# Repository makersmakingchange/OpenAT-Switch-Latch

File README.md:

<!--- Open Source Assistive Technology: GitHub Readme Template Version 1.2 (2024-May-27)  --->

<!--- TITLE --->
# OpenAT Switch Latch 
The OpenAT Switch Latch is a switch adapter that enables a standard momentary assistive switch to be used as a toggle switch or latch. Activating and releasing the input switch will turn on and hold on the output. Activating and releasing the input switch again will turn the connected output device off. The device requires one CR2032 coin cell battery for operation. 

This device was developed as several assistive switch users requested the ability to control lights and other devices in a semi-permanent manner utilizing their preferred momentary assistive switches.

The OpenAT Switch Latch is comprised of off-the-shelf electronics, a custom printed circuit board (PCB) and 3D printed parts.

The OpenAT Switch Latch is open assistive technology (OpenAT). Under the terms of the open source licenses, the device may be built, used, and improved upon by anyone.

The overall cost of materials for a single build is approximately $67 CAD. The cost of materials when built in quantity is $38 CAD.

> [!IMPORTANT]
2025-Nov-06: One of the electronic components in this design has been discontinued (MOSFET IRLD014PBF) and is no longer available on DigiKey or Mouser. In the short term, there are some alternative sources (e.g., https://www.amazon.ca/10PCS-IRLD110-DIP4-IRLD110PBF-DIP-4/dp/B0DSSJTPH8). In the longer term, we are working on updating the design with an alternative component.  

Last updated: 2026-Jan-12

## Usage
To setup the OpenAT Switch Latch, a momentary switch is plugged into the 3.5 mm jack marked 'Input' and the device to be controlled is plugged into the 3.5 mm jack marked 'Output'.

To use the device it must be powered on by sliding the Power Switch towards the left to the On position. When the assistive switch is activated, the LED indicator light will turn on and remain on, and the output device will be activated. When the assistive switch is activated again, the LED indicitor light will turn off and remain off, and the output device will be deactivated.

## More info at
- [Makers Making Change Library Page](https://www.makersmakingchange.com/s/product/switch-latch/01tJR00000095zlYAA)

## How to Obtain a OpenAT-Switch-Latch
### 1. Do it Yourself (DIY) or Do it Together (DIT)

This is an open-source assistive technology, so anyone is free to build it. All of the files and instructions required to build the OpenAT-Switch-Latch are contained within this repository. Refer to the Maker Checklist below.

### 2. Request a build of this device

If you would like to obtain a OpenAT Switch Latch, you may submit a build request through the [MMC Library Page](https://www.makersmakingchange.com/s/product/switch-latch/01tJR00000095zlYAA). The requestor is responsible for the cost of materials and any shipping.

### 3. How to build this device for someone else

If you have the skills and equipment to build this device, and would like to donate your time to create the switch for someone who needs it, visit the [MMC Maker Wanted](https://makersmakingchange.com/maker-wanted/) section.

## Getting Started

### 1. Read the Makers Checklist

The [Makers Checklist](/Documentation/OpenAT_Switch_Latch_Maker_Checklist.pdf) provides an overview of the steps required to build this device.

### 2. Order the Off-The-Shelf Components

The [Bill of Materials](/Documentation/OpenAT_Switch_Latch_BOM.csv) lists all of the parts and components required to build the OpenAT-Switch-Latch. The main switch component needs to be ordered online. The rest of the off-the-shelf components are also online or may be available in smaller quantities at your local hardware store or dollar store.

### 3. Order the PCBs

The [Gerber_Files](/Build_Files/PCB_Build_Files/Gerber_Files) includes the PCB build information which can be submitted to PCB fabrication service to create the custom PCB. Please refer to MMC-PCB for more information on custom PCB fabrication.

### 4. Print the 3D Printable components

All of the files and individual print files can be in the [/Build_Files/3D_Printing_Files](/Build_Files/3D_Printing_Files/) folder.

### 5. Assemble the OpenAT-Switch-Latch

Reference the [Assembly Guide](/Documentation/OpenAT_Switch_Latch_Assembly_Guide.pdf) for the tools and steps required to build each portion.

## Files

### Documentation
| Document             | Version | Link |
|----------------------|---------|------|
| Design Rationale     | 1.0     | [OpenAT_Switch_Latch_Design_Rationale](/Documentation/OpenAT_Switch_Latch_Design_Rationale.pdf)     |
| Maker Checklist      | 1.0     | [OpenAT_Switch_Latch_Maker_Checklist](/Documentation/OpenAT_Switch_Latch_Maker_Checklist.pdf)     |
| Bill of Materials    | 1.2.1    | [OpenAT_Switch_Latch_Bill_of_Materials](/Documentation/OpenAT_Switch_Latch_BOM.csv)     |
| 3D Printing Guide    | 1.0     | [OpenAT_Switch_Latch_3D_Printing_Guide](/Documentation/OpenAT_Switch_Latch_3D_Printing_Guide.pdf)     |
| Assembly Guide       | 1.2.1     | [OpenAT_Switch_Latch_Assembly_Guide](/Documentation/OpenAT_Switch_Latch_Assembly_Guide.pdf)     |
| User Guide           | 1.0     | [OpenAT_Switch_Latch_User_Guide](/Documentation/OpenAT_Switch_Latch_User_Guide.pdf)    |

### Design Files

 - [CAD Design Files](/Design_Files/CAD_Design_Files)
 - [PCB Design Files](/Design_Files/PCB_Design_Files)

### Build Files

 - [3D Printing Files](/Build_Files/3D_Printing_Files)
 - [PCB Build Files](/Build_Files/PCB_Build_Files)

## License
Copyright (c) 2023-2024 Neil Squire Society.

This repository describes Open Hardware:
 - Everything needed or used to design, make, test, or prepare the OpenAT Switch Latch is licensed under the [CERN 2.0 Weakly Reciprocal license (CERN-OHL-W v2) or later](https://cern.ch/cern-ohl ) .
  - Accompanying material such as instruction manuals, videos, and other copyrightable works that are useful but not necessary to design, make, test, or prepare the Forest Hub are published under a [Creative Commons Attribution-ShareAlike 4.0 license (CC BY-SA 4.0)](https://creativecommons.org/licenses/by-sa/4.0/) .

You may redistribute and modify this documentation and make products using it under the terms of the [CERN-OHL-W v2](https://cern.ch/cern-ohl).
This documentation is distributed WITHOUT ANY EXPRESS OR IMPLIED WARRANTY, INCLUDING OF MERCHANTABILITY, SATISFACTORY QUALITY AND FITNESS FOR A PARTICULAR PURPOSE.
Please see the CERN-OHL-W v2 for applicable conditions.

Source Location: https://github.com/makersmakingchange/OpenAT-Switch-Latch

## Contributors
 
 - Derrick Andrews, Neil Squire Society. Concept generation, circuit design, testing, documentation.
 - Milad Hajihassan, Neil Squire Society. PCB Layout.
 - Jake Mclvor, Neil Squire Society. Enclosure design, documentation. 

---

<!-- ABOUT MMC START -->
## About Makers Making Change

Makers Making Change is a program of [Neil Squire](https://www.neilsquire.ca/), a Canadian non-profit that uses technology, knowledge, and passion to empower people with disabilities.

Makers Making Change leverages the capacity of community based Makers, Disability Professionals and Volunteers to develop and deliver affordable Open Source Assistive Technologies.

 - Website: [www.MakersMakingChange.com](https://www.makersmakingchange.com/)
 - GitHub: [makersmakingchange](https://github.com/makersmakingchange)
 - Bluesky: [@makersmakingchange.bsky.social](https://bsky.app/profile/makersmakingchange.bsky.social)
 - Instagram: [@makersmakingchange](https://www.instagram.com/makersmakingchange)
 - Facebook: [makersmakechange](https://www.facebook.com/makersmakechange)
 - LinkedIn: [Neil Squire Society](https://www.linkedin.com/company/neil-squire-society/)
 - Thingiverse: [makersmakingchange](https://www.thingiverse.com/makersmakingchange/about)
 - Printables: [MakersMakingChange](https://www.printables.com/@MakersMakingChange)

### Contact Us
For technical questions, to get involved, or to share your experience we encourage you to [visit our website](https://www.makersmakingchange.com/) or [contact us](https://www.makersmakingchange.com/s/contact).
<!-- ABOUT MMC END -->

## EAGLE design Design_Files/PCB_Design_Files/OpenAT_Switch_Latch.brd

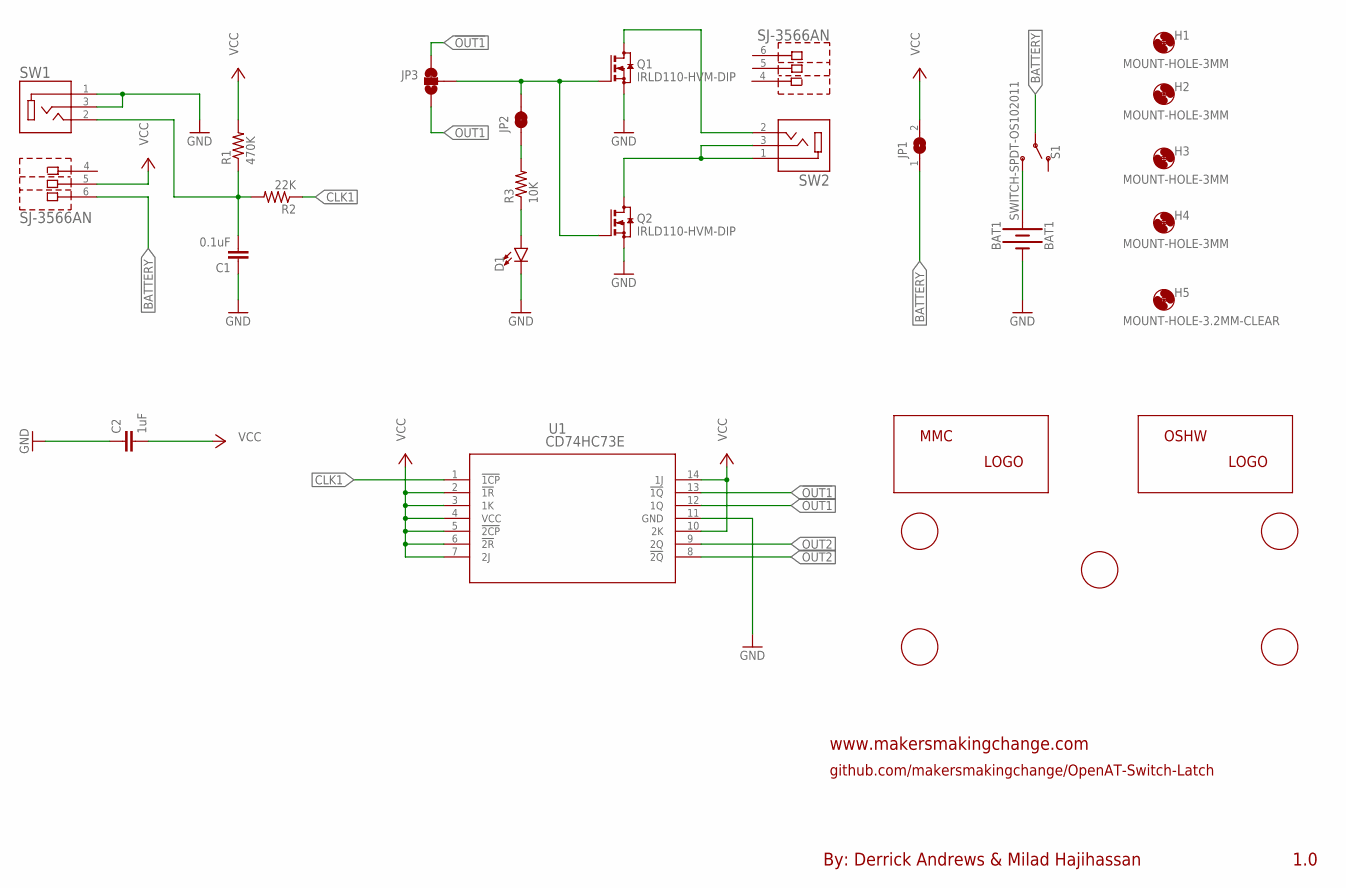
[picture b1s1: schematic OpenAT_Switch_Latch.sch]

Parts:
BAT1: BAT1; BATTCOM_20MM_PTH
C1: 0.1uF; CAP-050-030X075
C2: 1uF; CAP-050-030X075
D1: LED_5MM-5MM-GREEN; LED_5MM_GREEN
H1, H2, H3, H4: MOUNT-HOLE-3MM; HOLE-3MM
H5: MOUNT-HOLE-3.2MM-CLEAR; HOLE-3.2MM-CLEAR
JP1: SOLDERJUMPEROPENED; SOLDERJUMPER_OPENED_TRACE_SILK
JP2: JUMPERS-SMT_2_NC_TRACE_SILK; JUMPERS_SMT-JUMPER_2_NC_TRACE_SILK
JP3: JUMPERS-SMT_3_1-NC_TRACE_SILK; JUMPERS_SMT-JUMPER_3_1-NC_TRACE_SILK
LABEL_INPUT: MMC_LABEL-SW-INPUT; LABEL-INPUT
LABEL_LOGO: MMC_LOGO-SM; MMC_SMALL_LOGO
LABEL_OUTPUT: MMC_LABEL-SW-OUTPUT; LABEL-OUTPUT
Q1, Q2: IRLD110-HVM-DIP; HVM-DIP
R1: 470K; RESISTOR_0204/5
R2: 22K; RESISTOR_0204/5
R3: 10K; RESISTOR_0204/5
S1: SWITCH-SPDT-OS102011; SWITCH_SPDT_11MA1QS1
SW1, SW2: SJ-3566AN; CUI_SJ-3566AN
U1: CD74HC73E; 14-DIP
U$1: OSHW_LOGO-XSM; OSHW_X-SMALL_LOGO
U$2: MMC_LABEL-OPENAT; LABEL-OPENAT
U$3: MMC_LABEL-SWITCH-LATCH; LABEL-SWITCH-LATCH
U$4: MMC_LABEL-V1.0; LABEL-V1.0

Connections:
!OUT1: JP3.1, U1.13 (!1Q)
!OUT2: U1.8 (!2Q)
BATTERY: JP1.1, S1.2, SW1.6
CLK1: R2.1, U1.1 (!1CP)
GND: BAT1.-, C1.1, C2.1, D1.K (C), Q1.2 (S), Q2.2 (S), SW1.1, SW1.3, U1.11 (GND)
unnamed: BAT1.+, S1.3 (S)
unnamed: JP2.1, R3.2
unnamed: D1.A, R3.1
unnamed: Q2.3 (D), SW2.1, SW2.3
unnamed: Q1.3 (D), SW2.2
unnamed: C1.2, R1.1, R2.2, SW1.2
OUT1: JP3.3, U1.12 (1Q)
OUT1-SELECT: JP2.2, JP3.2, Q1.1 (G), Q2.1 (G)
OUT2: U1.9 (2Q)
VCC: C2.2, JP1.2, R1.2, SW1.5, U1.2 (!1R), U1.3 (1K), U1.4 (VCC), U1.5 (!2CP), U1.6 (!2R), U1.7 (2J), U1.10 (2K), U1.14 (1J)

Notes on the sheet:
www.makersmakingchange.com
1.0
By: Derrick Andrews & Milad Hajihassan
github.com/makersmakingchange/OpenAT-Switch-Latch

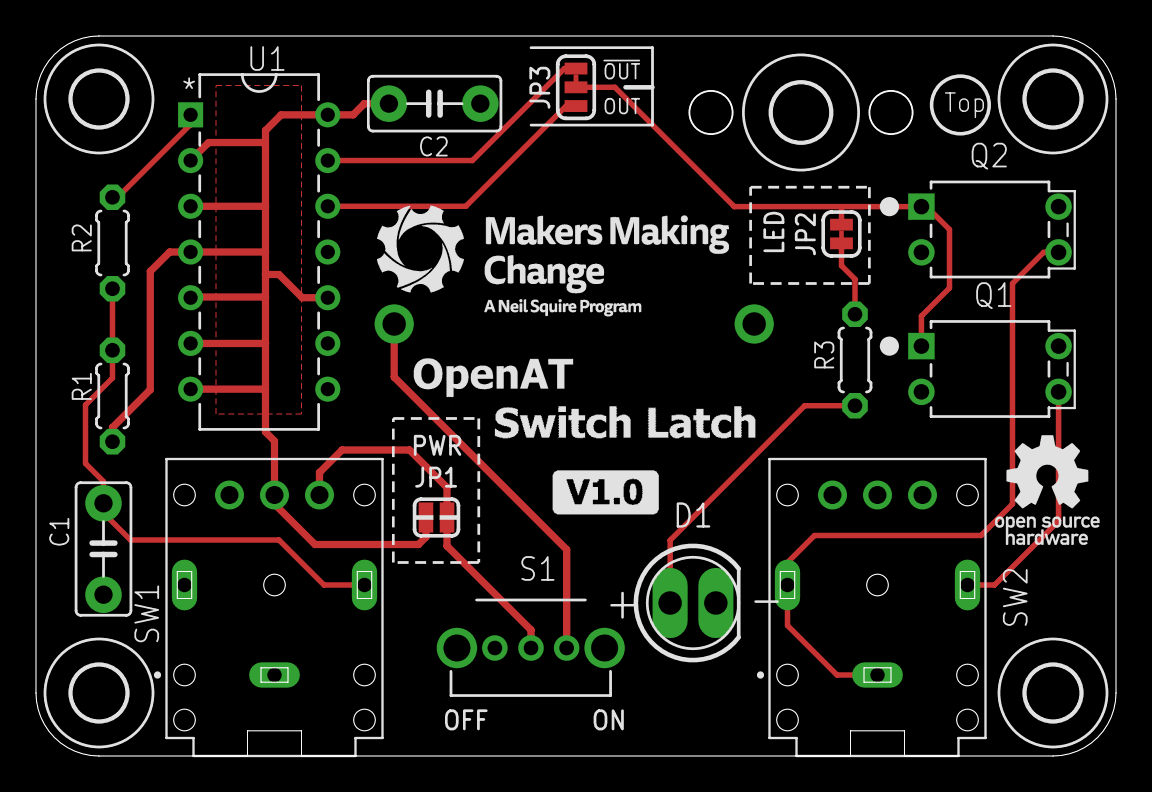
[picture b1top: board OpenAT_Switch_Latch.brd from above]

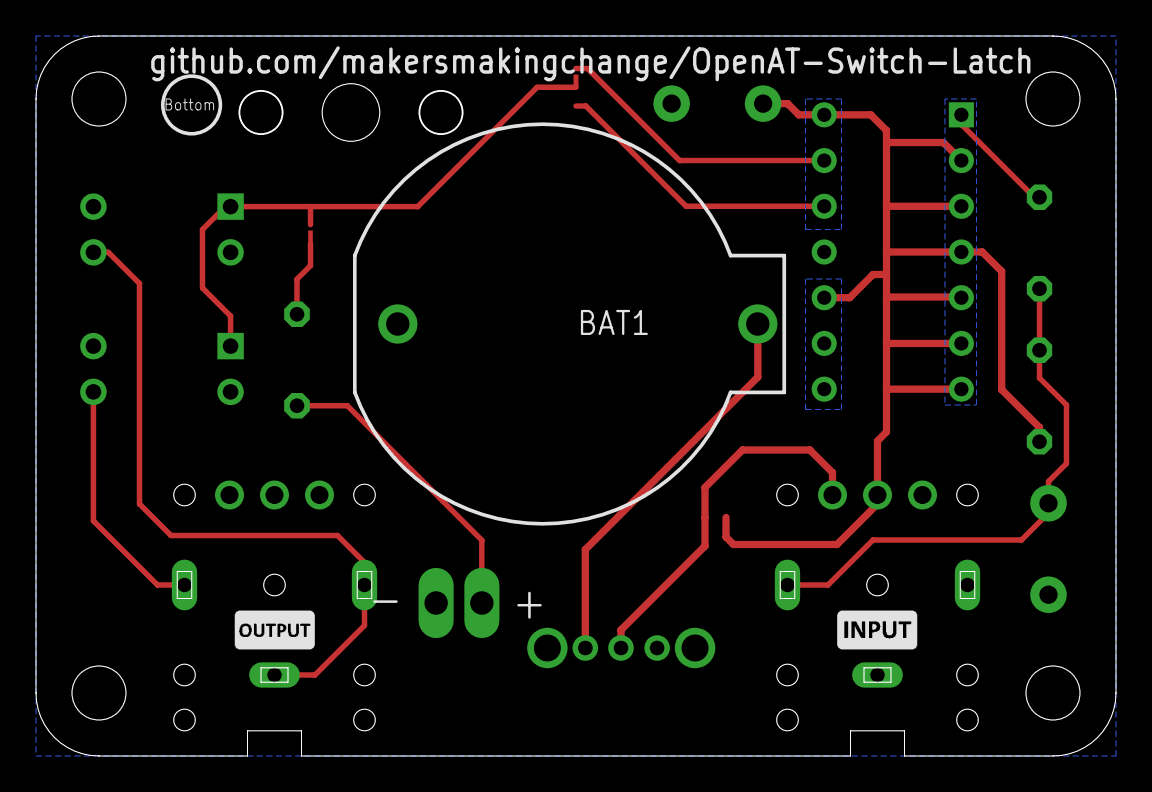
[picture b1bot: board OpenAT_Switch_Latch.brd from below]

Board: 2 copper layers, 59.9 x 39.9 mm, 28 parts (3 on the bottom side), 13 nets.

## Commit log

2023-01-28 OpenAT-Switch-Latch Version 1.0
2023-01-28 Updated readme image
2023-01-30 Updated document licensing
2023-02-22 Updated BOM file links
2023-02-28 Updated BOM file
2023-05-18 Update README.md
    Modify license
2023-09-14 Update README.md
    Remove forum link
2023-11-18 Clean up documentation naming
2023-11-18 Add licenses
2023-11-18 Update and clean-up CAD files
2023-11-18 Standardize naming
2023-11-18 Standardize folder naming
2023-11-18 Create CHANGES.txt
    create and update changes.txt
2023-11-18 Clean-up photos
2023-11-18 Remove photos to reduce repo size
2023-11-18 Update instructions
    - reordered steps to put LED insertion after other shorter components
    - fixed typos and incorrect photos
    - removed baked-in step numbers from photos
    - added alt text to all images
    - added battery to components list
    - added assistive switch and tape to tool list
2023-11-23 6th screw
    Update Assembly Guide to v1.1
    Update BOM to 1.02 (add 6th screw)
2023-11-23 Update assembly guide to V1.2
    - Replaced visual BOM with table.
    - Updated component numbers to match build order
    - captured and added photos of battery and screws
2023-11-23 Update OpenAT_Switch_Latch_Assembly_Guide.pdf
    Clean pdf
2024-08-26 Fix assembly guide typos
    Mosfet Q1 & Q2: shows qty = 1 instead of 2
    Flip-Flop IC: no number for Qty
    Green LED: shows qty = 3 instead of 1
2024-08-26 Update README.md
    V1.2.1
2024-10-10 Capacitor 3D Model Change
    Update capacitor package in PCB with smaller package
2024-10-10 Create graphic to aid LED placement
    Create Fusion drawing and Inkscape illustration to aid LED installation
2024-10-10 Update Assembly Guide
    Updated assembly guide:
    1. Added LED installation graphic and additional warning.
    2. Re-arranged steps to install battery in holder before soldering to hold assembly together.
    3. Added troubleshooting steps.
2025-04-10 Add Update About MMC GitHub Action
2025-04-12 Update About MMC Section
2025-05-23 Update Battery_Cover.stl
    Updated design with unsupported hole
2025-05-23 Update CAD files
2026-01-12 Revise last updated date and component notice
    Updated last updated date and added note about discontinued component.

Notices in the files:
parts and their libraries:
COPYRIGHT: Copyright (C) 2022 Ultra Librarian. All rights reserved.
